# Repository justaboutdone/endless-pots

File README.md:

# Endless Pots

**The secret 360º endless-potentiometers that  make rotary encoders obsolete**

*Wait a minute...! There are endlessly rotating pots? But how does that work and why didn't I (nor the internet) know about them?*

We recently stumbled across the existence of endless pots, analog rotary potentiometers that can be turned not just once, but an infinite number of times. These can be used to read out the absolute position (and thus also relative angle changes over time) with high accuracy (analog read out).
And no, we don't mean rotary encoders, which usually have a poor operating feel and can only measure rotation digitally and in discrete steps. 

When we realized that the internet seems to have a blind spot to this topic, we decided to share our researched knowledge so that everyone can ~~throw away their stupid rotary encoders~~ start using endless pots in their devices. :)

# Documentation

*This article will assume you understand the basics of using* [*normal potentiometers*](https://en.wikipedia.org/wiki/Potentiometer) *with a single wiper, and that you have experience programming Arduinos.*

### Prelude by Connor

**I recently embarked on an Arduino project** that required rotary encoders – or so I thought. And I wasn’t so happy about it, because I *really* dislike rotary encoders. The affordable ones have click-steps and are usually limited to 20-30 steps – unless you want to dish out some serious cash – and even then, they’re bulky, harder to program, and nearly impossible to multiplex. 

While trying to find non-shitty encoders, a thought popped into my mind… “Didn’t I used to have a MIDI controller with like, *16 smooth encoders?!”* 

Ah yes, the **APC40 mk1**! Sure enough, it has 16 damn encoders with LED rings! And even with an 8x5 clip launcher, tons of buttons, 9 faders and a cross-fader, it was still relatively affordable. So, where can I get these magically cheap, perfectly smooth encoders?!

This question sent me down one of the deepest internet rabbit-holes I’ve ever been on. And odds are, if you’re reading this now, you’re in the same position. 

### The Alpha 360º Endless Potentiometer

**The secret is the Alpha 360º Endless Potentiometer with two wipers.** 

Prices can vary a lot (from $1 in special offers to $4.24 on Mouser) and the pots are offered under many different names. We already bought [these](https://de.aliexpress.com/item/1005007005315736.html?spm=a2g0o.order_list.order_list_main.5.4b065c5fZVxfd8&gatewayAdapt=glo2deu) (which recently just jumped up in price???) and [these](https://de.aliexpress.com/item/1005007005688361.html) and can confirm they work properly and have good turning resistance. 

They almost certainly are the [RV112FF-40B1 model](https://www.taiwanalpha.com/downloads?target=products&id=79), but we can't say for sure as they are sold under different names. Very often they are sold with terms like "Alpha Boss GT10", "MPK, MPD, APC rotary pot", etc. to show that they can be used as replacement parts for these products.

We also bought [some of this other model](https://www.taiwanalpha.com/downloads?target=products&id=93) from Mouser, which are the same, but also include a push-switch, so you can click the knob in like a button. However, the turning-resistance on these is very weak, which makes them feel much cheaper than the non-switch model. As it is pretty cool to have the push function, we are working on solutions to artificially add torque by e.g. sticking foam to the pot caps… It's a work in progress.

### Pins

Unlike normal potentiometers, these 360º pots have *4 pins* for the wipers. Two of them are ground and voltage like a normal pot, but instead of having just one pin for the analog read out, there are *two*. This is because there are two wipers (variable resistors), which are offset from each other. Using the analog data you get from both pins, you can find the absolute position of the knob in radians.

Pins ① and ③ are ground and voltage, and pins ② and 2 are analog data. You’ll have to experiment until you get them in the correct direction.

### Signal Path of the Wipers

Getting the aboslute position from the two analog read pins isn't as easy as it may seem. We provide a basic Arduino script that can read any number of these pots (two pots in the example) and report their absolute values as MIDI or Serial. The key is the [2-argument arctangent function](https://en.wikipedia.org/wiki/Atan2), aka **atan2**. Using this with the values from both wipers gives you the position of the knob from -pi to +pi. 

The second example we provide is a generic PCB with 8 of these pots connected to ADCs. They read the wipers and pass the values on to an ESP32, where a similar calculation is done to get the angle change since the last cycle. This can then be sent via Serial (or other protocols) to a computer to only trigger relative changes on a parameter...

## Links and Sources

When we started researching this topic, we couldn't really find a source. This was partly because we used the wrong terms. We went back and collected all the forums and discussions on the topic when we were preparing this repo. Here are the most important ones (unorganized, maybe we'll do that later). Some of them already contain the right clues if you look closely ;-) Many thanks for the work of others so far! 

- [components - Is there something such as an infinite potentiometer? - Electrical Engineering Stack Exchange](https://electronics.stackexchange.com/questions/374040/is-there-something-such-as-an-infinite-potentiometer) 
- [Driver/algorithm for 360 deg endless potentiometer | Hackaday.io](https://hackaday.io/project/171841-driveralgorithm-for-360-deg-endless-potentiometer) 
- [Convert dual pot "360 endless pot" to angle position](https://gist.github.com/todbot/cd964282dd3c2599a629f5ecf5d1ca98) 
- [Endless potentiometer decoding - Software Development - Daisy Forums](https://forum.electro-smith.com/t/endless-potentiometer-decoding/3972) 
- [GeroTakke.de - ottopot](https://gerotakke.de/ottopot/)
- [help endless potentiometers](https://www.xsimulator.net/community/threads/help-endless-potentiometers.12218/)  
- [Read Endless Potentiometer | Teensy Forum](https://forum.pjrc.com/index.php?threads/read-endless-potentiometer.59830/)

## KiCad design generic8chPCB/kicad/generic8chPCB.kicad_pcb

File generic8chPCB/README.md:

# Generic 8 Channel PCB Design with ESP32

This PCB reads the **relative angle change of 8 endless potentiometers between each cycle**. 

## The Board

In [/kicad](/kicad) you can find a KiCAD schematic and board file. This board however has not been tested yet, but is similar to generic8chPCBwithButtons placed next to this directory, which we sucessfully build and tested (but didn't yet have time to upload, check the license, etc.).

The board uses a [Seeed Studio XIAO ESP32-C3](https://wiki.seeedstudio.com/XIAO_ESP32C3_Getting_Started/) microcontroller to retrieve the sixteen 12-bit analog reads from two [MCP3208](https://www.microchip.com/en-us/product/mcp3208) ADCs via SPI and then sends the calculated angle changes (e.g. to a computer) as one serial message per cycle. Reading and smoothing the values, calculating the position of each knob and sending the whole array takes only about **1 microsecond**. 

This is certainly technical overkill, but with little hardware experience it seemed to be the simplest and most reliable solution to us. Feel free to comment, if you have ideas that make this PCB better.

## The Code

The core of the code is the atan2 function, which receives the two analog measured values of the two wipers of one potentiometer and returns the absolute position of the knob between -pi and +pi. The relative angle change compared to the last reading is calculated from this and sent via the serial interface together with the changes of the other potentiometers.

I am using the Arduino IDE to upload the code. You need to install the ESP32 board in Arduino and the following libraries:

```Arduino
#include <SPI.h>
#include <Mcp320x.h>
#include <ResponsiveAnalogRead.h>
```

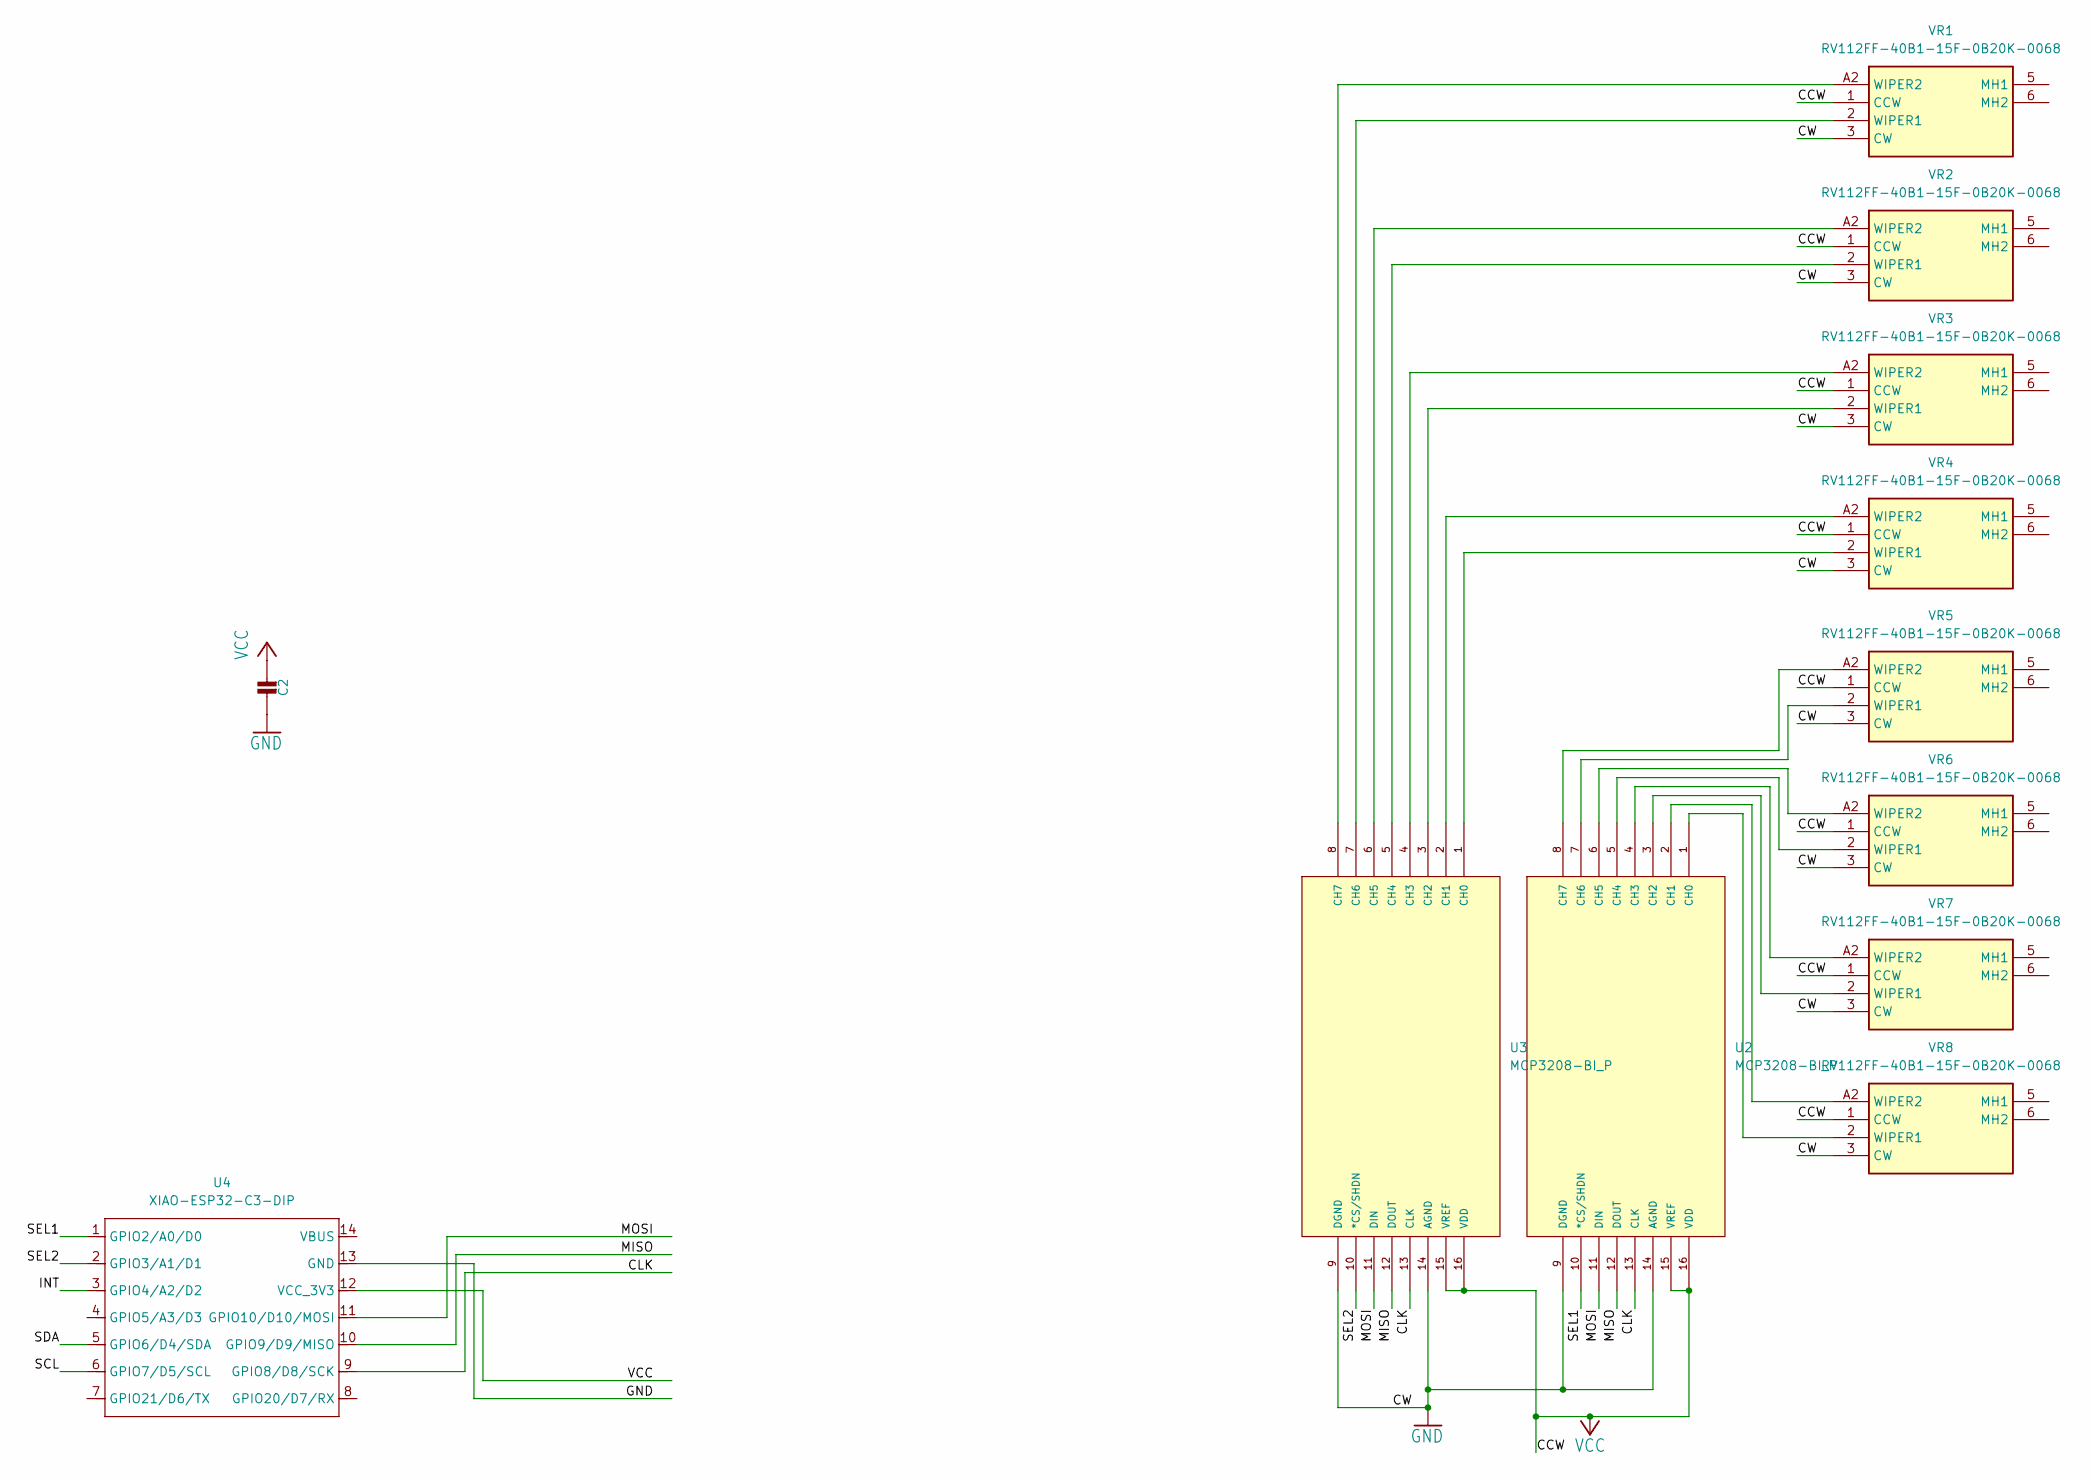
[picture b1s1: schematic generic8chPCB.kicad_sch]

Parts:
C2: 10uF; _0805
U2, U3: MCP3208-BI_P; SOIC-16_3.9x9.9mm_P1.27mm
U4: XIAO-ESP32-C3-DIP; MCU_Seeed_ESP32C3
VR1, VR2, VR3, VR4, VR5, VR6, VR7, VR8: RV112FF-40B1-15F-0B20K-0068; RV112FF40B115F0B20K0068; Mouser Part Number 317-1240FF-15F-0B20K

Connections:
/CLK: U2.13 (CLK), U3.13 (CLK), U4.9 (GPIO8/D8/SCK)
/INT: U4.3 (GPIO4/A2/D2)
/MISO: U2.12 (DOUT), U3.12 (DOUT), U4.10 (GPIO9/D9/MISO)
/MOSI: U2.11 (DIN), U3.11 (DIN), U4.11 (GPIO10/D10/MOSI)
/SCL: U4.6 (GPIO7/D5/SCL)
/SDA: U4.5 (GPIO6/D4/SDA)
/SEL1: U2.10 (*CS/SHDN), U4.1 (GPIO2/A0/D0)
/SEL2: U3.10 (*CS/SHDN), U4.2 (GPIO3/A1/D1)
GND: C2.1, U2.9 (DGND), U2.14 (AGND), U3.9 (DGND), U3.14 (AGND), U4.13 (GND), VR1.3 (CW), VR2.3 (CW), VR3.3 (CW), VR4.3 (CW), VR5.3 (CW), VR6.3 (CW), VR7.3 (CW), VR8.3 (CW)
unnamed: U2.1 (CH0), VR8.2 (WIPER1)
unnamed: U2.2 (CH1), VR8.A2 (WIPER2)
unnamed: U2.3 (CH2), VR7.2 (WIPER1)
unnamed: U2.4 (CH3), VR7.A2 (WIPER2)
unnamed: U2.5 (CH4), VR6.2 (WIPER1)
unnamed: U2.6 (CH5), VR6.A2 (WIPER2)
unnamed: U2.7 (CH6), VR5.2 (WIPER1)
unnamed: U2.8 (CH7), VR5.A2 (WIPER2)
unnamed: U3.1 (CH0), VR4.2 (WIPER1)
unnamed: U3.2 (CH1), VR4.A2 (WIPER2)
unnamed: U3.3 (CH2), VR3.2 (WIPER1)
unnamed: U3.4 (CH3), VR3.A2 (WIPER2)
unnamed: U3.5 (CH4), VR2.2 (WIPER1)
unnamed: U3.6 (CH5), VR2.A2 (WIPER2)
unnamed: U3.7 (CH6), VR1.2 (WIPER1)
unnamed: U3.8 (CH7), VR1.A2 (WIPER2)
VCC: C2.2, U2.15 (VREF), U2.16 (VDD), U3.15 (VREF), U3.16 (VDD), U4.12 (VCC_3V3), VR1.1 (CCW), VR2.1 (CCW), VR3.1 (CCW), VR4.1 (CCW), VR5.1 (CCW), VR6.1 (CCW), VR7.1 (CCW), VR8.1 (CCW)

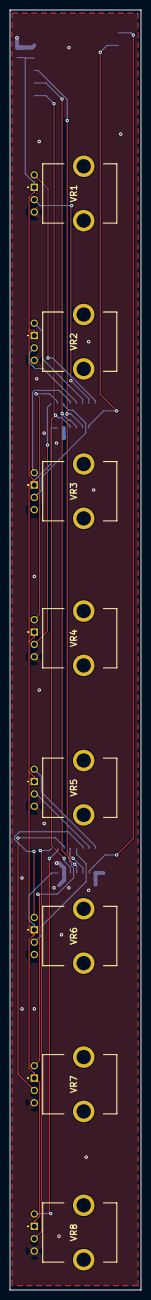
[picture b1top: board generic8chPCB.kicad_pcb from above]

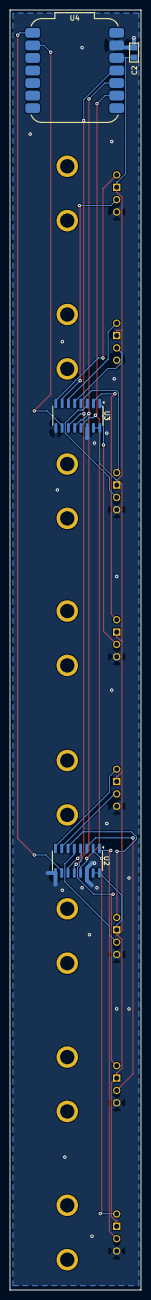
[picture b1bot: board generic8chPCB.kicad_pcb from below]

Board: 2 copper layers, 26.5 x 259.0 mm, 12 parts (4 on the bottom side), 23 nets.

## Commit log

2024-12-26 Init README.md
2024-12-26 test edit redame
2024-12-26 add story and imgs to readme
2024-12-26 add Arduino code
2024-12-27 Rename receiveTwoPots.amxd to pot_partner.amxd
2024-12-27 Rename pot_partner.amxd to potPartner.amxd
2024-12-27 Auto stash before merge of "main" and "origin/main"
2024-12-27 add generic 8ch code
2024-12-27 add 8ch pcb with buttons
2024-12-27 add links to README
2024-12-30 Create LICENSE
2025-12-27 create photos folders
2025-12-27 Create test
